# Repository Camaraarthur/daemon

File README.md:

<div align="center">
  
  <h1>daemon</h1>
  <p><strong>One AI agent. Terminal access to every device you own.</strong></p>
  <p>Open source &bull; Multi-device &bull; Free tier included &bull; Bring your own keys</p>

  <a href="https://daemon.page">Website</a> &bull;
  <a href="https://daemon.page/download">Download</a> &bull;
  <a href="SPEC.md">Spec</a> &bull;
  <a href="docs/">Docs</a>
</div>

---

## What is Daemon?

Daemon connects all your devices -- laptop, phone, server -- into one AI-powered workspace. Chat with your daemon, and it runs commands on any connected device, syncs your clipboard, deploys your apps, and remembers everything across sessions.

**Free tier**: Qwen3-Coder via OpenRouter. No credit card needed.
**Bring your own key**: Paste your Anthropic/OpenAI/DeepSeek key.
**Link Claude Max**: Use your $100/mo subscription through Daemon.

## Quick Start

```bash
# Install on any device (macOS, Linux, Windows)
curl -sSL daemon.page/install.sh | bash

# Pair with your account
daemon pair <CODE>  # Get code at daemon.page/download

# That's it. Your device is connected.
```

## Features

- **Multi-device mesh** -- Connect phone, laptop, server. Run commands on any device from anywhere.
- **Clipboard sync** -- Copy on your phone, paste on your laptop. Automatic.
- **One-click deploy** -- `/deploy` publishes to username.daemon.page instantly.
- **Persistent memory** -- Your daemon remembers across sessions. Never re-explain context.
- **Slash commands** -- `/commit`, `/deploy`, `/review`, `/search` -- power tools built in.
- **Your data stays yours** -- Local-first. Open source. Self-hostable.
- **Any model** -- Qwen (free), DeepSeek, Claude, GPT -- bring your own keys.
- **Native apps** -- Android, Windows, macOS, Linux. Same experience everywhere.

## How it works

<div align="center">
  
</div>

1. Install daemon on your devices
2. Each device connects via WebSocket to the daemon server
3. Chat with your AI -- it can run commands on any connected device
4. Deploy apps, sync files, search memory -- all through one conversation

## vs. Alternatives

| | Daemon | Claude Code | Cursor | Windsurf |
|---|---|---|---|---|
| Multi-device | All devices | One terminal | One IDE | One IDE |
| Free tier | Qwen unlimited | $20+/mo | $20/mo | $15/mo |
| Deploy apps | your.daemon.page | -- | -- | -- |
| Clipboard sync | Cross-device | -- | -- | -- |
| Memory | Persistent | Session only | -- | -- |
| Open source | MIT | -- | -- | -- |
| Self-hostable | Docker compose | -- | -- | -- |
| BYOK | Any provider | Anthropic only | Multiple | Multiple |

## Architecture

Daemon is a monorepo with four main components:

- **`web/`** -- Next.js web UI and API server (port 4800)
- **`cli/`** -- Cross-platform device bridge (Node.js)
- **`android/`** -- Native Android app (Kotlin/Jetpack Compose)
- **`desktop/`** -- Desktop bridge (Tauri/Rust)
- **`protocol/`** -- Shared protocol types (TypeScript)

The server coordinates WebSocket connections between devices and routes AI requests through a 3-tier model router (free Qwen -> mid DeepSeek -> premium Claude/GPT via BYOK).

See [SPEC.md](SPEC.md) for the full v0 specification (7,300 words covering protocol, security, agent architecture, and deployment).

## Self-hosting

```bash
git clone https://github.com/arthurcamara/daemon.git
cd daemon
docker compose up -d
```

Requires: Node.js 20+, SQLite. See [docs/](docs/) for detailed setup.

## Contributing

We welcome contributions. Daemon is built in the open.

- Read [CONTRIBUTING.md](CONTRIBUTING.md) before making changes
- Read [SPEC.md](SPEC.md) for architecture decisions
- Follow the rules in [CLAUDE.md](CLAUDE.md)

## License

[MIT](LICENSE) -- Copyright 2026 Arthur Camara

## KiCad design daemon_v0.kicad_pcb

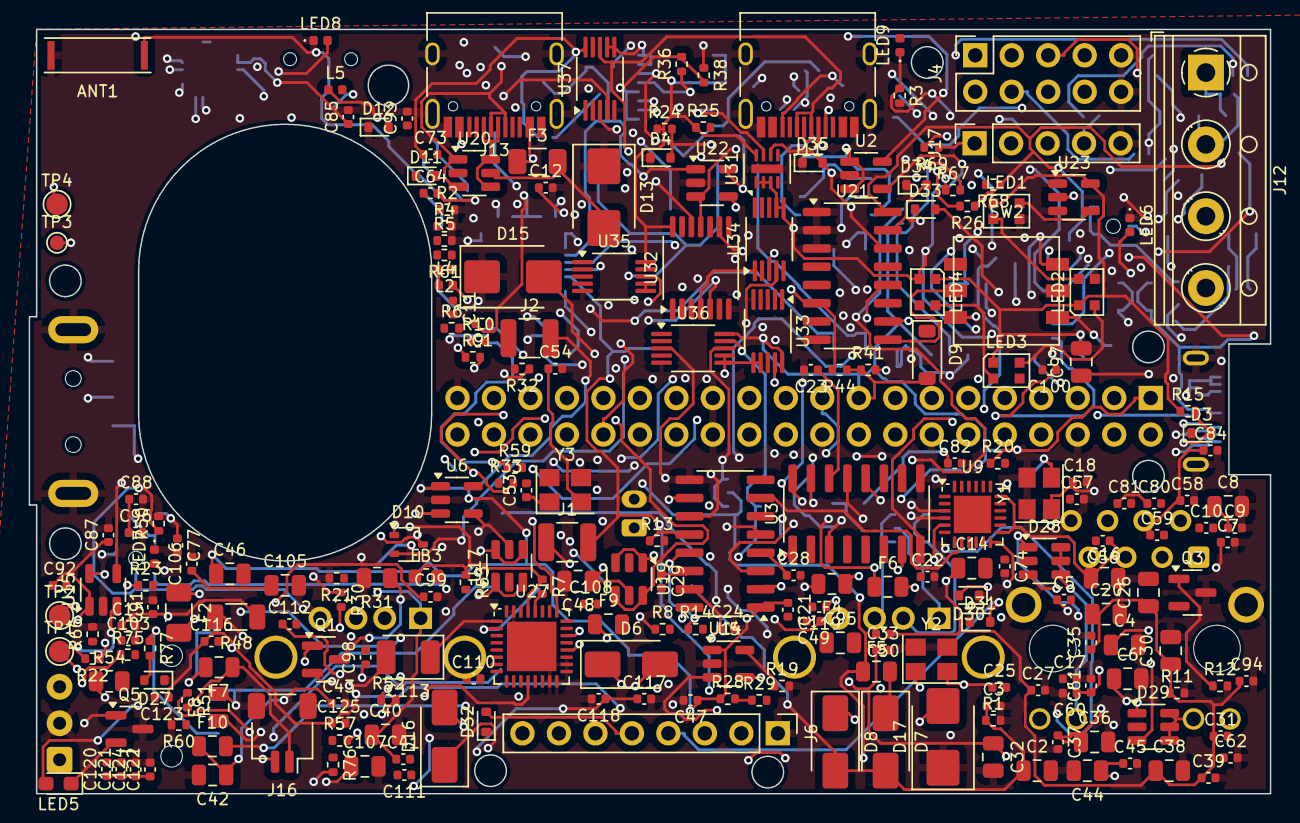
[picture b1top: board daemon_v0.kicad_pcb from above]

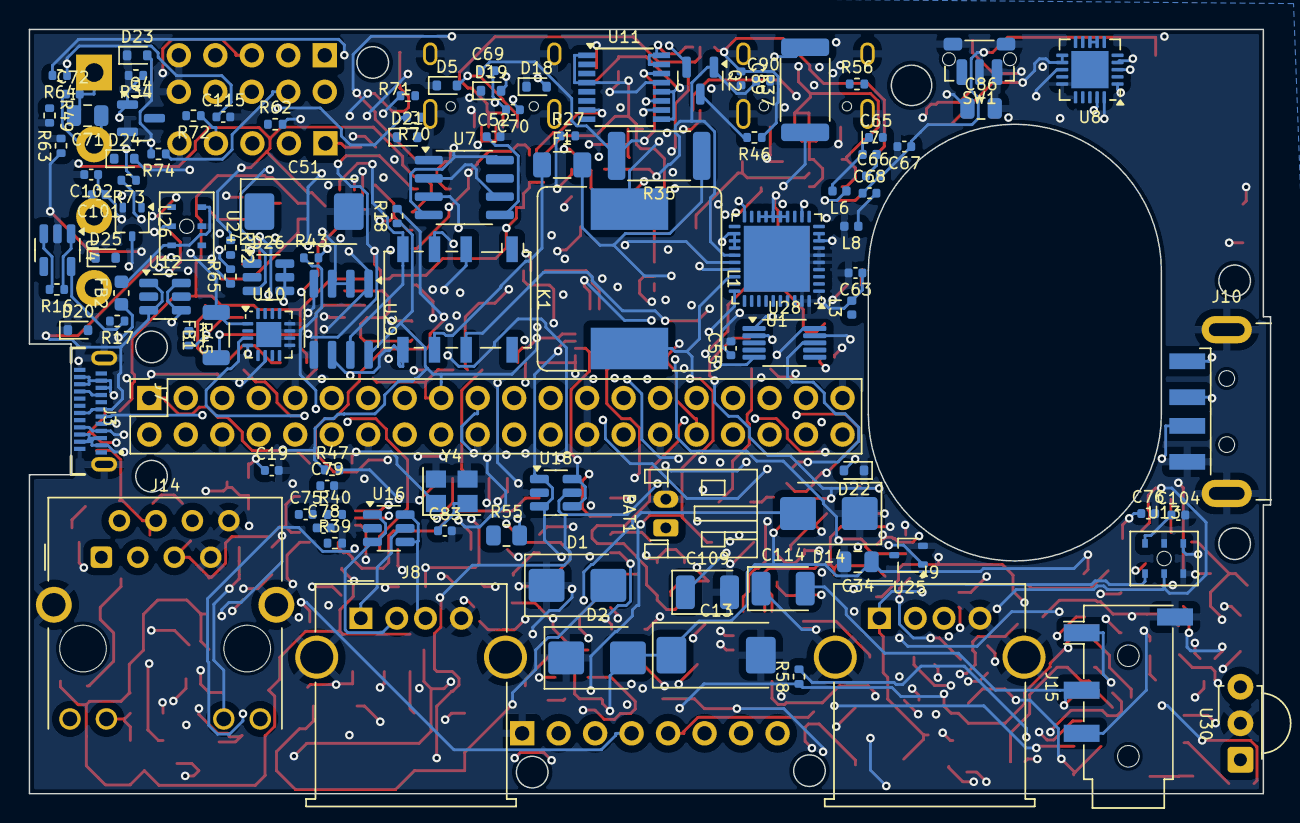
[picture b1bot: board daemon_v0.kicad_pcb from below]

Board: 4 copper layers, 86.4 x 53.2 mm, 338 parts (106 on the bottom side), 217 nets.

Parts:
ANT1: 915MHz Chip Antenna; Antenna_Chip_Johanson_0915AT43A0026
BAT1: Li-ion Battery; JST_PH_S2B-PH-K_1x02_P2.00mm_Horizontal
C1, C3, C5, C7, C9, C10, C11, C15, C17, C21, C22, C23, C27, C28, C29, C31, C33, C35, C37, C39, C41, C43, C45, C47, C49, C50, C55, C56, C57, C72, C73, C75, C77, C79, C81, C84, C85, C87, C88, C89, C90, C91, C92, C93, C94, C96, C100, C101, C102, C103, C104, C106, C108, C110, C115, C116, C117, C119, C120, C121, C122, C123, C124, C125: 100n; C_0402_1005Metric
C2, C4, C8, C14, C16, C20, C26, C30, C32, C34, C36, C38, C40, C42, C44, C46, C48, C71, C86, C95, C97, C105, C107: 10u; C_0805_2012Metric
C6: 22u; C_0805_2012Metric
C12, C74, C76, C78, C80, C118: 4u7; C_0402_1005Metric
C13, C51: 100u; CP_EIA-7343-31_Kemet-D
C18, C19, C24, C25: 22p; C_0402_1005Metric
C52, C69, C70: 10n; C_0402_1005Metric
C53, C54, C82, C83: 27p; C_0402_1005Metric
C58, C59, C60, C61, C66: 100p; C_0402_1005Metric
C62: 1p0; C_0402_1005Metric
C63, C64: 1p5; C_0402_1005Metric
C65: 3p3; C_0402_1005Metric
C67: 12p; C_0402_1005Metric
C68: 47p; C_0402_1005Metric
C98, C99: 1n; C_0402_1005Metric
C109, C113, C114: 100u; CP_EIA-3528-21_Kemet-B
C111, C112: 1u; C_0402_1005Metric
D1: TVS 5V_SYS Clamp; D_SMB
D2: TVS VIN Clamp; D_SMB
D3: ESD Port1 CC; D_SOD-523
D4: ESD Port5 CC1; D_SOD-523
D5: ESD Port5 CC2; D_SOD-523
D6: SS34 Charge Port1→VIN; D_SMA
D7: SS34 Charge Port4→VIN; D_SMA
D8: SS34 Charge Port5→VIN; D_SMA
D9: TVS ISO Input Clamp; D_SOD-123
D10: ESD Goobay CC1; SOT-323_SC-70
D11: ESD Goobay CC2; D_SOD-523
D12, D18, D19, D20, D21, D22, D23, D24, D25, D27, D30, D31, D32, D33, D34, D35: ESD5Z3.3; D_SOD-523
D13, D14, D15, D17: SMBJ5.0A; D_SMB
D16: SS34; D_SMA
D26, D28, D29: SM712; SOT-23-6
F1: PTC ISO Ch1 60Ω; Fuse_1206_3216Metric
F2: PTC ISO Ch2 60Ω; Fuse_1206_3216Metric
F3: PTC_1A; Fuse_1206_3216Metric
F4, F5, F6, F9, F10: PTC_500mA; Fuse_0805_2012Metric
F7, F8: PTC_200mA; Fuse_0805_2012Metric
FB1: 5V_AUDIO Ferrite 1.5A; L_1206_3216Metric
FB2: MIC_VDD Ferrite; L_0603_1608Metric
FB3: BLM18AG601SN1; L_0603_1608Metric
J1: Battery PTC 2A Fuse; R_1210_3225Metric
J2: 10mΩ Current Sense; R_1210_3225Metric
J3: 40-Pin Radxa Header; PinSocket_2x20_P2.54mm_Vertical
J4: AUX GPIO Breakout; PinSocket_2x05_P2.54mm_Vertical
J6: ST7789 SPI Display; MillMax_1x08_P2.54mm_Vertical
J7: USB-C♂ Plug → Radxa (KEY); USB_C_Plug_GCT_USB4155
J8: USB-A♀ Host Port 2; USB_A_Molex_67643_Horizontal
J9: USB-A♀ Host Port 3; USB_A_Molex_67643_Horizontal
J10: USB-A♂ Charge Port 4; USB_A_CNCTech_1001-011-01101_Horizontal
J11: USB-C♀ Main Port 5; USB_C_Receptacle_HRO_TYPE-C-31-M-12
J12: WAGO 4P Field Terminal; TerminalBlock_RND_205-00014_1x04_P5.00mm_Horizontal
J13: USB-C♀ Goobay Bridge; USB_C_Receptacle_HRO_TYPE-C-31-M-12
J14: RJ45 MagJack; RJ45_Hanrun_HR911105A_Horizontal
J15: TRRS 3.5mm Jack; Jack_3.5mm_PJ320D_Horizontal
J16: Speaker JST; JST_SH_SM02B-SRSS-TB_1x02-1MP_P1.00mm_Horizontal
J17: Analog-In; PinSocket_1x05_P2.54mm_Vertical
K1: G6K-2F-Y; Relay_DPDT_Omron_G6K-2F-Y
L1: 2.2uH Boost Inductor; L_Bourns_SRR1260
L2, L3, L6, L7: 12n; L_0402_1005Metric
L4, L5: 18n; L_0402_1005Metric
L8: 3n3; L_0402_1005Metric
LED1: WS2812B Status 1; LED_WS2812B-2020_PLCC4_2.0x2.0mm
LED2: WS2812B Status 2; LED_WS2812B-2020_PLCC4_2.0x2.0mm
LED3: WS2812B Status 3; LED_WS2812B-2020_PLCC4_2.0x2.0mm
LED4: WS2812B Status 4; LED_WS2812B-2020_PLCC4_2.0x2.0mm
LED5: IR Blaster LED; LED_0603_1608Metric_Pad1.05x0.95mm_HandSolder
LED6: Mic Recording Red 1; LED_0402_1005Metric
LED7: Mic Recording Red 2; LED_0402_1005Metric
LED8: Power Green LED; LED_0402_1005Metric
LED9: AMBER_0402; LED_0402_1005Metric
Q1: BC857 Dummy Load PNP; SOT-23
Q2: BSS84 Wake PMOS; SOT-23
Q3: 2N7002 PMIC Kill NMOS; SOT-23
Q4: AO3400A IR Drive NMOS; SOT-23
Q5: AO3400A; SOT-23
R1, R3, R4, R5, R49, R63: 100k; R_0402_1005Metric
R2, R11, R12, R16, R18, R20, R22, R26, R30, R33, R39, R40, R41, R42, R43, R44, R45, R46, R53, R57, R61, R62, R67, R68, R69, R70: 10k; R_0402_1005Metric
R6: 51k; R_0402_1005Metric
R7, R8: 4.7k; R_0402_1005Metric
R9, R10: 470; R_0402_1005Metric
R13, R14: 15k; R_0402_1005Metric
R15: 12k; R_0402_1005Metric
R17: 3.3k; R_0402_1005Metric
R19, R21, R23, R27: 13k; R_0402_1005Metric
R24, R25, R32: 56k; R_0402_1005Metric
R28, R50: 47k; R_0402_1005Metric
R29: 150; R_0402_1005Metric
R31: 82; R_0805_2012Metric
R34, R36: 562; R_0402_1005Metric
R35, R37: 562; R_2512_6332Metric
R38: 12.1k; R_0402_1005Metric
R47, R65, R66: 100; R_0402_1005Metric
R48: 100k; R_1206_3216Metric
R51, R52: 10R; R_0402_1005Metric
R54, R55: 1k; R_0805_2012Metric
R56, R71, R72, R73, R74, R75, R76, R77: 1k; R_0402_1005Metric
R58: 0R_DNP; R_0402_1005Metric
R59: 2.2k; R_0402_1005Metric
R60: 0; R_0402_1005Metric
R64: 120; R_0402_1005Metric
SW1: Power Button; SW_Push_1P1T-MP_NO_Horizontal_Alps_SKRTLAE010
SW2: 5-Way Nav Switch; SW_Alps_SKRHABE010
TP1: TP VIN; TestPoint_Pad_D1.5mm
TP2: TP BAT; TestPoint_Pad_D1.5mm
TP3: TP LX; TestPoint_Pad_D1.0mm
TP4: TP VSYS; TestPoint_Pad_D1.5mm
U1: IP5328P PMIC; QFN-40-1EP_6x6mm_P0.5mm_EP4.6x4.6mm
U2: AP2112K 3.3V LDO; SOT-23-5
U3: SL2.1A USB Hub 1; SOIC-16_3.9x9.9mm_P1.27mm
U4: SY6280 Port1 Radxa Key; SOT-23-5
U5: SY6280 Port2 USB-A♀; SOT-23-5
U6: SY6280 Port3 USB-A♀; SOT-23-5
U7: NE555 Heartbeat Timer; SOIC-8_3.9x4.9mm_P1.27mm
U8: CC1101 Sub-GHz Radio; QFN-20-1EP_4x4mm_P0.5mm_EP2.6x2.6mm
U9: RTL8152B Ethernet; QFN-24-1EP_4x4mm_P0.5mm_EP2.6x2.6mm
U10: MAX98357A I2S Amp; QFN-16-1EP_3x3mm_P0.5mm_EP1.75x1.75mm
U11: ISO1212 Dual Isolator; SSOP-16_3.9x4.9mm_P0.635mm
U12: ESD USB Port1; SOT-23-6
U13: INMP441 Mic Left; InvenSense_INMP441_BottomPort
U14: SL2.1A USB Hub 2; SOIC-16_3.9x9.9mm_P1.27mm
U15: SY6280 Port4 USB-A♂; SOT-23-5
U16: ESD USB Port2; SOT-23-6
U17: ESD USB Port3; SOT-23-6
U18: ESD USB Port4; SOT-23-6
U19: ESD USB Port5; SOT-23-6
U20: ESD Goobay Bridge; SOT-23-6
U21: PCF8574 I2C GPIO Exp; SOIC-16_3.9x9.9mm_P1.27mm
U22: SY6280 Port5 USB-C♀; SOT-23-5
U23: 3.3→5V Level Shifter; SOT-23-5
U24: INMP441 Mic Right; InvenSense_INMP441_BottomPort
U25, U26: ESD9B5.0ST5G; SOT-323_SC-70
U27: NAU88C22; QFN-32-1EP_5x5mm_P0.5mm_EP3.45x3.45mm
U28: ADS1115; MSOP-10_3x3mm_P0.5mm
U29: SP3485; SOIC-8_3.9x4.9mm_P1.27mm
U30: TSOP38238; Vishay_MINICAST-3Pin
U31: ATECC608B; DFN-8-1EP_2x3mm_P0.5mm_EP0.61x2.2mm
U32: 74LVC04A; TSSOP-14_4.4x5mm_P0.65mm
U33, U34, U35, U36, U37: TS3USB221; VSSOP-10_3x3mm_P0.5mm
Y1: 12MHz Hub1 Xtal; Crystal_SMD_3225-4Pin_3.2x2.5mm
Y2: 12MHz Hub2 Xtal; Crystal_SMD_3225-4Pin_3.2x2.5mm
Y3: 27MHz CC1101 Xtal; Crystal_SMD_3225-4Pin_3.2x2.5mm
Y4: 25MHz Ethernet Xtal; Crystal_SMD_3225-4Pin_3.2x2.5mm

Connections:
3V3_CLEAN: C16.1, C17.1, C56.1, C57.1, C58.1, C59.1, C60.1, C61.1, C84.1, C85.1, C86.1, J14.4, J14.5, R33.1, R40.1, U2.5, U8.7, U8.8, U8.11, U8.12, U8.19, U9.1, U9.10, U9.13, U9.18
3V3_J4_OUT: F9.2, J4.1
3V3_SYS: C73.1, C88.1, C89.1, C95.1, C96.1, C115.1, C116.1, C119.1, C120.1, C121.1, C122.1, C123.1, C124.1, C125.1, D9.2, F9.1, FB2.1, FB3.1, J3.1, J3.17, J6.2, K1.1, R7.1, R8.1, R18.1, R20.1, R22.1, R24.1, R25.1, R26.1, R41.1, R42.1, R43.1, R44.1, R45.1, R46.1, R47.1, R53.1, R58.1, R59.1, R64.1, R68.1, U11.1, U11.4, U21.16, U27.29, U28.8, U29.8, U31.8, U32.14, U33.10, U34.10, U35.10, U36.10, U37.10
5V_AUDIO: C97.1, C101.1, C102.1, FB1.2, U10.1
5V_J4_OUT: F10.2, J4.2
5V_SYS: C13.1, C14.1, C15.1, C20.1, C21.1, C26.1, C27.1, C30.1, C31.1, C34.1, C35.1, C38.1, C39.1, C42.1, C43.1, C46.1, C47.1, C50.1, C87.1, C90.1, C91.1, C92.1, C93.1, C94.1, D2.2, F10.1, FB1.1, J2.2, LED1.1, LED2.1, LED3.1, LED4.1, Q1.1, Q2.1, R11.1, R15.1, R16.1, R28.1, R48.1, U1.25, U2.1, U2.3, U3.1, U4.1, U5.1, U6.1, U7.4, U7.8, U9.11, U14.1, U15.1, U22.1, U23.5
ADC_ADDR: R63.1, U28.1
ADC_AIN0: D18.2, R69.2, U28.4
ADC_AIN0_P: J17.1, R69.1
ADC_AIN1: D19.2, R70.2, U28.5
ADC_AIN1_P: J17.2, R70.1
ADC_AIN2: D20.2, R71.2, U28.6
ADC_AIN2_P: J17.3, R71.1
ADC_AIN3: D21.2, R72.2, U28.7
ADC_AIN3_P: J17.4, R72.1
ADC_ALRT: R64.2, U28.2
AMP_OUT_N: R55.1, U10.13, U26.1
AMP_OUT_N_FILT: C99.1, R52.1, R55.2
AMP_OUT_P: R54.1, U10.15, U25.1
AMP_OUT_P_FILT: C98.1, R51.1, R54.2
AMP_SD: C100.1, R53.2, R56.2, U10.3
AUX_GPIO_1: D22.2, J3.8, R73.2, U29.4
AUX_GPIO_1_P: J4.3, R73.1
AUX_GPIO_2: D23.2, J3.10, R74.2, U29.1
AUX_GPIO_2_P: J4.4, R74.1
AUX_GPIO_3: D24.2, J3.11, R65.1, R75.2
AUX_GPIO_3_P: J4.5, R75.1
BAT: BAT1.1, C4.1, C5.1, D16.1, TP2.1
BAT_ISO: D17.2, J1.2, L1.2, U1.28
BAT_PROTECTED: D16.2, J1.1
BJT_BASE: Q1.2, R30.2
BJT_COLLECTOR: Q1.3, R31.1
CODEC_ADCOUT: R61.1, U27.24
CODEC_AVDD: C105.1, C106.1, FB3.2, U27.5
CODEC_DVDD: C107.1, C108.1, U27.20
CODEC_LHPOUT: C113.1, U27.1
CODEC_LMICN: R60.1, U27.6
CODEC_LMICP: C112.2, U27.7
CODEC_MICBIAS: C111.1, R62.1, U27.13
CODEC_RHPOUT: C114.1, U27.2
CODEC_VREF: C109.1, C110.1, U27.12
ETH_MDI_RXN: D29.3, J14.6, U9.5
ETH_MDI_RXP: D29.1, J14.3, U9.4
ETH_MDI_TXN: D28.3, J14.2, U9.3
ETH_MDI_TXP: D28.1, J14.1, U9.2
ETH_XI: C82.1, U9.21, Y4.1
ETH_XO: C83.1, U9.22, Y4.2
GND: ANT1.2, BAT1.2, C2.2, C3.2, C4.2, C5.2, C6.2, C7.2, C8.2, C9.2, C10.2, C11.2, C12.2, C13.2, C14.2, C15.2, C16.2, C17.2, C18.2, C19.2, C20.2, C21.2, C22.2, C23.2, C24.2, C25.2, C26.2, C27.2, C28.2, C29.2, C30.2, C31.2, C32.2, C33.2, C34.2, C35.2, C36.2, C37.2, C38.2, C39.2, C40.2, C41.2, C42.2, C43.2, C44.2, C45.2, C46.2, C47.2, C48.2, C49.2, C50.2, C51.2, C52.2, C53.2, C54.2, C55.2, C56.2, C57.2, C58.2, C59.2, C60.2, C61.2, C62.2, C63.2, C65.2, C67.2, C73.2, C74.2, C75.2, C76.2, C77.2, C78.2, C79.2, C80.2, C81.2, C82.2, C83.2, C84.2, C85.2, C86.2, C87.2, C88.2, C89.2, C90.2, C91.2, C92.2, C93.2, C94.2, C95.2, C96.2, C97.2, C98.2, C99.2, C100.2, C101.2, C102.2, C103.2, C104.2, C105.2, C106.2, C107.2, C108.2, C109.2, C110.2, C111.2, C115.2, C116.2, C117.2, C118.2, C119.2, C120.2, C121.2, C122.2, C123.2, C124.2, C125.2, D1.1, D2.1, D3.1, D4.1, D5.1, D11.1, D12.1, D13.1, D14.1, D15.1, D17.1, D18.1, D19.1, D20.1, D21.1, D22.1, D23.1, D24.1, D25.1, D26.2, D27.1, D28.2, D29.2, D30.1, D31.1, D32.1, D33.1, D34.1, D35.1, J3.6, J3.9, J3.14, J3.20, J3.25, J3.26, J3.30, J3.39, J4.9, J4.10, J6.1, J7.A1, J7.A8, J7.A12, J7.B1, J7.B5, J7.B8, J7.B12, J7.S1, J7.S2, J8.4, J8.5, J9.4, J9.5, J10.4, J10.5, J11.A1, J11.A8, J11.A12, J11.B1, J11.B8, J11.B12, J11.S1, J13.A1, J13.A8, J13.A12, J13.B1, J13.B8, J13.B12, J13.S1, J14.7, J14.8, J14.SH, J15.S, J16.MP, J17.5, L8.2, LED1.3, LED2.3, LED3.3, LED4.3, LED6.1, LED7.1, LED8.1, Q3.3, Q4.2, Q5.3, R1.2, R2.2, R3.2, R4.2, R5.2, R6.2, R11.2, R12.2, R13.2, R14.2, R17.2, R19.2, R21.2, R23.2, R27.2, R31.2, R32.2, R34.2, R39.2, R49.2, R50.2, R60.2, R63.2, R66.2, SW1.1, SW1.2, SW1.MP, SW2.Common, U1.1, U1.4, U1.5, U1.6, U1.7, U1.29, U1.38, U1.39, U1.40, U1.41, U2.2, U3.9, U4.2, U5.2, U6.2, U7.1, U8.14, U8.15, U8.16, U8.21, U9.6, U9.14, U9.15, U9.17, U9.20, U9.25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
GOOBAY_CC1: D11.2, J13.A5, U1.2
GOOBAY_CC2: D12.2, J13.B5, U1.3
GOOBAY_VBUS_FUSED: F3.1, J13.A4, J13.A9, J13.B4, J13.B9
HB_TMR_CTRL: C52.1, U7.5
HB_TMR_NODE_A: R28.2, R29.1, U7.7
HB_TMR_OUT: R30.1, U7.3
HB_TMR_THR: C51.1, R29.2, U7.2, U7.6
HUB1_DN_DM_1: U3.6, U33.4
HUB1_DN_DM_1_SW: J7.A7, J7.B7, U12.1, U12.3, U33.9
HUB1_DN_DM_2: U3.8, U34.4
HUB1_DN_DM_2_SW: J8.2, U16.1, U16.3, U34.9
HUB1_DN_DM_3: U3.11, U35.4
HUB1_DN_DM_3_SW: J9.2, U17.1, U17.3, U35.9
HUB1_DN_DM_4: U3.13, U14.3
HUB1_DN_DP_1: U3.5, U33.3
HUB1_DN_DP_1_SW: J7.A6, J7.B6, U12.4, U12.6, U33.8
HUB1_DN_DP_2: U3.7, U34.3
HUB1_DN_DP_2_SW: J8.3, U16.4, U16.6, U34.8
HUB1_DN_DP_3: U3.10, U35.3
HUB1_DN_DP_3_SW: J9.3, U17.4, U17.6, U35.8
HUB1_DN_DP_4: U3.12, U14.2
HUB1_VDD18: C23.1, U3.14
HUB1_VDD33: C22.1, U3.4
HUB1_XI: C18.1, U3.15, Y1.1
HUB1_XO: C19.1, U3.16, Y1.2
HUB2_DN_DM_1: U14.6, U36.4
HUB2_DN_DM_1_SW: J10.2, U18.1, U18.3, U36.9
HUB2_DN_DM_2: U9.7, U14.8
HUB2_DN_DM_3: U14.11, U37.4
HUB2_DN_DM_3_SW: J11.A7, J11.B7, U19.1, U19.3, U37.9
HUB2_DN_DM_4: R14.1, U14.13
HUB2_DN_DP_1: U14.5, U36.3
HUB2_DN_DP_1_SW: J10.3, U18.4, U18.6, U36.8
HUB2_DN_DP_2: U9.8, U14.7
HUB2_DN_DP_3: U14.10, U37.3
HUB2_DN_DP_3_SW: J11.A6, J11.B6, U19.4, U19.6, U37.8
HUB2_DN_DP_4: R13.1, U14.12
HUB2_VDD18: C29.1, U14.14
HUB2_VDD33: C28.1, U14.4
HUB2_XI: C24.1, U14.15, Y2.1
HUB2_XO: C25.1, U14.16, Y2.2
I2C1_PMIC_SCL: R10.2, U1.11
I2C1_PMIC_SDA: R9.2, U1.12
I2C1_SCL: D35.2, J3.5, R8.2, R10.1, U21.14, U27.27, U28.10, U31.6
I2C1_SDA: D34.2, J3.3, R7.2, R9.1, U21.15, U27.28, U28.9, U31.5
I2S_BCLK: J3.13, U10.7, U13.3, U24.3, U27.22
I2S_DATA_IN: J3.38, R50.1, R61.2, U13.5, U24.5
I2S_DATA_OUT: J3.40, U10.6, U27.25
I2S_LRCLK: J3.35, U10.8, U13.4, U24.4, U27.23
IP5328P_BST: C1.1, U1.19
IP5328P_LIGHT: LED9.1, R3.1, U1.20
IP5328P_NTC: R6.1, U1.10
IP5328P_RSET: R2.1, U1.21
IP5328P_VBUS: C8.1, C9.1, D13.2, F3.2, U1.32, U20.5
IP5328P_VBUSG: C10.1, U1.33
IP5328P_VING: C11.1, U1.31
IP5328P_VOUT1G: R4.1, U1.36
IP5328P_VOUT2G: R5.1, U1.35
IP5328P_VREG: C12.1, U1.27
IP5328P_VSYS: C6.1, C7.1, J2.1, TP4.1, U1.8, U1.9, U1.22, U1.23, U1.24, U1.34, U1.37
IR_GPIO: D25.2, Q5.1, R49.1, R76.2
IR_GPIO_P: J4.6, R76.1
IR_LED_N: LED5.1, Q5.2
IR_LED_P: LED5.2, R48.2
IR_RX: U21.12, U30.1
IR_VS_FILT: C117.1, C118.1, R68.2, U30.3
ISO_DO1: J3.28, U11.2
ISO_GND1: C69.2, C70.2, C71.2, C72.2, D10.2, J12.1, R36.2, R38.2, U11.9, U11.12
ISO_IN1: C69.1, R35.2, U11.14
ISO_IN1_PTCA: D10.1, F1.2, R35.1
ISO_IN1_RAW: F1.1, K1.6
ISO_IN2: C70.1, R37.2, U11.11
ISO_IN2_PTCA: D10.3, F2.2, R37.1
ISO_IN2_RAW: F2.1, K1.3
ISO_SENSE1: R36.1, U11.13
ISO_SENSE2: R38.1, U11.10
ISO_VCC1: C71.1, C72.1, J12.2
LED_DIN: LED1.4, U23.4
LX: C1.2, L1.1, TP3.1, U1.14, U1.15, U1.16, U1.17, U1.18
MCU_LED_DIN: J3.36, U23.2
MIC_LED_A: LED6.2, LED7.2, R57.2
MIC_VDD: C103.1, C104.1, FB2.2, R57.1, U13.1, U24.1, U24.6
NAV_CENTER: Q2.3, R46.2, SW2.Center, U21.9
NAV_DOWN: R43.2, SW2.C, U21.5
NAV_LEFT: R44.2, SW2.B, U21.6
NAV_RIGHT: R45.2, SW2.D, U21.7
NAV_UP: R42.2, SW2.A, U21.4
NC: D26.4, D26.5, D26.6, D28.4, D28.5, D28.6, D29.4, D29.5, D29.6, J7.A2, J7.A3, J7.A10, J7.A11, J7.B2, J7.B3, J7.B10, J7.B11, J14.9, J14.10, J14.11, J14.12, LED4.2, U2.4, U10.4, U11.7, U11.15, U11.16, U25.3, U26.3, U31.1, U31.2, U31.3, U31.7, U32.12, U33.6, U33.7, U34.6, U34.7, U35.6, U35.7, U36.6, U36.7, U37.6, U37.7
PCF8574_INT: J3.27, R47.2, U21.13
PMIC_KEY: Q2.2, Q3.2, SW1.1, U1.26
PMIC_KILL: J3.37, Q3.1, R12.1
PMIC_LIGHT_LED: LED9.2, R59.2
PWR_LED_A: LED8.2, R58.2
RADXA_GPIO_5V: J3.2, J3.4
RF_ANT: ANT1.1, C66.2, C67.1, C68.1
RF_ANT_N: L3.1, U8.9
RF_ANT_P: L2.1, U8.10
RF_ANT_PRE: C66.1, L7.2
RF_BAL_N: C63.1, L3.2, L5.1
RF_BAL_P: C62.1, C64.1, L2.2, L4.1
RF_CLK: J3.16, U8.1
RF_CS_N: J3.18, R33.2, U8.4
RF_DCOUPL: C55.1, U8.13
RF_FILT_MID: C65.1, L6.2, L7.1
RF_GDO0: U8.6, U21.11
RF_MISO: J3.15, U8.3
RF_MOSI: J3.12, U8.2
RF_NOTCH: C68.2, L8.1
RF_RBIAS: R32.1, U8.20
RF_SE_50: C64.2, L4.2, L5.2, L6.1
RF_XI: C53.1, U8.17, Y3.1
RF_XO: C54.1, U8.18, Y3.2
RLY_COIL_N: D9.1, K1.8, Q4.3
RS485_A: D26.1, J4.7, K1.5, R67.1, U29.6
RS485_B: D26.3, J4.8, K1.4, R67.2, U29.7
RS485_DE: R65.2, R66.1, U29.2, U29.3
RTL_AVDD10: C80.1, C81.1, U9.23
RTL_DVDD10: C78.1, C79.1, U9.16
RTL_DVDD10_UPS: C76.1, C77.1, U9.12
RTL_LANWAKEB: R40.2, U9.19
RTL_RSET: R39.1, U9.24
RTL_U2VDD10: C74.1, C75.1, U9.9
SCREEN_BL: J3.7, J6.8
SCREEN_DC: D33.2, J3.32, J6.6
SCREEN_RST: D32.2, J3.22, J6.5
SPI3_CLK: D30.2, J3.23, J6.3
SPI3_CS: J3.24, J6.7, R41.2
SPI3_MOSI: D31.2, J3.19, J6.4
SPK_N: F8.1, J16.2, R52.2
SPK_N_FUSED: C114.2, F8.2, J15.R1
SPK_P: F7.1, J16.1, R51.2
SPK_P_FUSED: C113.2, F7.2, J15.T
STINGER1_CC: D3.2, J7.A5, R15.2
STINGER5_CC1: D4.2, J11.A5, R24.2
STINGER5_CC2: D5.2, J11.B5, R25.2
STINGER_EN_1: J3.29, R16.2, U4.3, U32.1
STINGER_EN_2: J3.31, R18.2, U5.3, U32.3
STINGER_EN_3: J3.33, R20.2, U6.3, U32.5
STINGER_EN_4: J3.21, R22.2, U15.3, U32.9
STINGER_EN_5: R26.2, U21.10, U22.3, U32.11
STINGER_ISET_1: R17.1, U4.5
STINGER_ISET_2: R19.1, U5.5
STINGER_ISET_3: R21.1, U6.5
STINGER_ISET_4: R23.1, U15.5
STINGER_ISET_5: R27.1, U22.5
STINGER_OE_1: U32.2, U33.1
STINGER_OE_2: U32.4, U34.1
STINGER_OE_3: U32.6, U35.1
STINGER_OE_4: U32.8, U36.1
STINGER_OE_5: U32.10, U37.1
TRRS_RING2: C112.1, J15.R2, R62.2, R77.1
TRRS_RING2_P: D27.2, R77.2
USB_UP_DM: J13.A7, J13.B7, U3.3, U20.1, U20.3
USB_UP_DP: J13.A6, J13.B6, U3.2, U20.4, U20.6
USB_VBUS_1: C32.1, C33.1, F4.1, J7.A4, J7.A9, J7.B4, J7.B9, U4.4, U12.5
USB_VBUS_1_FUSED: D6.1, F4.2
USB_VBUS_2: C36.1, C37.1, D14.2, J8.1, U5.4, U16.5
USB_VBUS_3: C40.1, C41.1, D15.2, J9.1, U6.4, U17.5
USB_VBUS_4: C44.1, C45.1, F5.1, J10.1, U15.4, U18.5
USB_VBUS_4_FUSED: D7.1, F5.2
USB_VBUS_5: C48.1, C49.1, F6.1, J11.A4, J11.A9, J11.B4, J11.B9, U19.5, U22.4
USB_VBUS_5_FUSED: D8.1, F6.2
VIN: C2.1, C3.1, D1.2, D6.2, D7.2, D8.2, R1.1, TP1.1, U1.30
WAGO_COM1: J12.3, K1.7
WAGO_COM2: J12.4, K1.2
WAGO_MODE: J3.34, Q4.1, R34.1
WS2812B_DOUT_1: LED1.2, LED2.4
WS2812B_DOUT_2: LED2.2, LED3.4
WS2812B_DOUT_3: LED3.2, LED4.4

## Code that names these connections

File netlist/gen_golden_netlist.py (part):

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    "SPI3_CLK", "SPI3_MOSI",
    # RF SoftSPI bus (CC1101)
    "RF_CLK", "RF_MOSI", "RF_MISO",
    "RF_CS_N", "RF_GDO0", "RF_GDO2",  # GDO1 = SO pin (shared with RF_MISO)
    "RF_XI", "RF_XO", "RF_RBIAS", "RF_DCOUPL",
    "RF_ANT_P", "RF_ANT_N", "RF_ANT",
    # CC1101 filterbalun internal nodes (TI DN017 / SWRA168A 3-stage diff→SE→T-filter)
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    "AMP_OUT_P_FILT", "AMP_OUT_N_FILT",
    "AMP_SD", "SPK_P", "SPK_N", "MIC_VDD", "MIC_LED_A",
    # WS2812B + IR blaster
    "MCU_LED_DIN",  # 3.3V Radxa GPIO → 74AHCT1G125 level shifter input
    "LED_DIN",      # 5V output of level shifter → first WS2812B DIN
    "WS2812B_DOUT_1", "WS2812B_DOUT_2", "WS2812B_DOUT_3",
    "IR_GPIO", "IR_LED_P", "IR_LED_N",
    # Power indicator LED
    "PWR_LED_A",
    # AUX GPIO expansion
    "AUX_GPIO_1", "AUX_GPIO_2", "AUX_GPIO_3",  # AUX_GPIO_4 removed (sacrificed for STINGER_EN_3)
    # PCF8574 interrupt line (open-drain, pulled to 3V3_SYS; connect to GPIO for IRQ-driven nav)
    "PCF8574_INT",
    # Power UX (A6)
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    "ISO_IN1_RAW", "ISO_IN2_RAW",
    "ISO_IN1_PTCA", "ISO_IN2_PTCA",
    "ISO_IN1", "ISO_IN2",
    "ISO_SENSE1", "ISO_SENSE2",  # SENSE pins: R_SENSE connects SENSE→FGND for threshold setting
    "ISO_SUB1", "ISO_SUB2",      # SUB pins: floating copper islands (isolation barrier)
    "ISO_DO1", "ISO_DO2",
    # Heartbeat timer (G)
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    "STINGER1_CC",
    # Radxa GPIO 5V rail (pins 2,4) — intentionally NOT connected to 5V_SYS.
    # Radxa outputs its own 5V here once running; we isolate it from Daemon's rail.
    "RADXA_GPIO_5V",
    # NAU88C22 audio codec (L)
    "CODEC_LHPOUT", "CODEC_RHPOUT", "CODEC_LSPKOUT", "CODEC_RSPKOUT",
    "CODEC_LMICP", "CODEC_LMICN", "CODEC_RMICP", "CODEC_RMICN",
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    # ADC protected inputs
    "ADC_AIN0_P", "ADC_AIN1_P", "ADC_AIN2_P", "ADC_AIN3_P",
    # GPIO protected
    "AUX_GPIO_1_P", "AUX_GPIO_2_P", "AUX_GPIO_3_P", "IR_GPIO_P",
    # Audio protected
    "SPK_P_FUSED", "SPK_N_FUSED", "TRRS_RING2_P",
    # Ethernet protected
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    # J4 fused power outputs
    "3V3_J4_OUT", "5V_J4_OUT",
    # WAGO switchable bypass
    "WAGO_COM1", "WAGO_COM2",  # Relay common pins (from WAGO pins 3/4)
    "WAGO_MODE",               # GPIO: LOW=industrial, HIGH=RS-485
    "RLY_COIL_N",              # Relay coil negative (BSS138 drain)
]

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    #   Pins 24,25: VSP/VSN (current sense)
    #   Pin 26:     KEY (button)
    #   Pin 27:     VREG (internal 3.1V LDO)
    #   Pin 28:     BAT (battery)
    #   Pin 29:     AGND (analog ground)
    #   Pin 30:     VIN (micro-USB input detect)
    #   Pin 31:     VING (VIN PMOS gate)
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    # Physical power button
    add(_next_ref("SW"), "SW_PWR", FP_SW_PUSH, "Switch", "SW_Push",
        [("1","PMIC_KEY"),("2","GND"),("MP","GND")])
    # J5 (PWR_MGMT header) removed — PMIC_KILL now routed via J3 pin 37
    # Software reboot: `sudo reboot` (warm SoC reset, no PMIC needed)
    # Software shutdown: drive J3.37 HIGH → Q3 pulls PMIC_KEY → IP5328P off

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        # DFP host: Rp pull-up (12k → 1.5A per USB-C Table 4-25) + higher ISET (3.3k → 2.06A)
        # D+/D- → Hub1 port 1 downstream: Radxa appears as USB device to laptop via Goobay.
        # Removing this plug from the Radxa cuts all power to the SBC — physical key.
        # Stinger GPIOs (STINGER_EN_1-5 via J3) control power switches — no USB host needed.
        ("U4",  1, FP_USB_C_PLUG,   "Connector", "USB_C_Plug_USB2.0",
         "HUB1_DN_DP_1", "HUB1_DN_DM_1", True,  "Rp", "3.3k"),
        ("U5",  2, FP_USB_A_FEMALE, "Connector", "USB_A",
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         ("A0","GND"),("A1","GND"),("A2","GND"),
         ("P0","NAV_UP"),("P1","NAV_DOWN"),("P2","NAV_LEFT"),("P3","NAV_RIGHT"),
         ("P4","NAV_CENTER"),
         ("P5","STINGER_EN_5"),  # GPIO-controlled USB-C female port 5 enable
         ("P6","RF_GDO0"),      # CC1101 interrupt (sync word / RX ready)
         ("P7","IR_RX"),         # IR receiver (TSOP38238) demodulated output
         ("INT","PCF8574_INT")])
    # PCF8574 bypass cap
    add(_next_ref("C"), "100n", FP_C0402, "Device", "C", [("1","3V3_SYS"),("2","GND")])
    # PCF8574 INT pull-up (10k to 3V3_SYS) — open-drain; keeps INT high (inactive) when no nav
    # event. Wire PCF8574_INT to a Radxa GPIO to enable interrupt-driven nav detection.
    add(_next_ref("R"), "10k", FP_R0402, "Device", "R", [("1","3V3_SYS"),("2","PCF8574_INT")])

    # ======================================================================
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    add(_next_ref("LED"), "VSMB294008", FP_IR_LED, "Device", "LED",
        [("A","IR_LED_P"),("K","IR_LED_N")])
    add(_next_ref("Q"), "AO3400A", FP_NFET_SOT23, "Device", "Q_NMOS_GDS",
        [("G","IR_GPIO"),("D","IR_LED_N"),("S","GND")])
    # IR LED current limit: need to stay within resistor rating for worst-case DC stuck-on.
    # 100Ω → I=38mA, P=0.14W → use 1206 (0.25W, ample margin). 38mA is still good for IR blast.
    add(_next_ref("R"), "100", "Resistor_SMD:R_1206_3216Metric", "Device", "R",
        [("1","5V_SYS"),("2","IR_LED_P")])
    # IR_GPIO pull-down (100k) — prevent spurious IR flash during Radxa boot
    add(_next_ref("R"), "100k", FP_R0402, "Device", "R",
        [("1","IR_GPIO"),("2","GND")])

    # ======================================================================
    # F: 40-Pin Radxa Expansion Header (PinSocket)
    # ======================================================================
    add("J3", "Radxa-40Pin", FP_RADXA_HDR, "Connector_Generic", "Conn_02x20_Odd_Even",
        [("1","3V3_SYS"),        ("2","RADXA_GPIO_5V"),
         ("3","I2C1_SDA"),       ("4","RADXA_GPIO_5V"),
         ("5","I2C1_SCL"),  ("6","GND"),
         ("7","SCREEN_BL"), ("8","AUX_GPIO_1"),   # was NAV_UP (→ PCF8574)
         ("9","GND"),       ("10","AUX_GPIO_2"),   # was NAV_DOWN (→ PCF8574)
         ("11","AUX_GPIO_3"),("12","RF_MOSI"),      # GPIO3_A2/I2S3_MCLK — soft SPI (not BCLK!)
         ("13","I2S_BCLK"),  ("14","GND"),         # GPIO3_A3/I2S3_SCLK_M0 — HW I2S bit clock
         ("15","RF_MISO"),  ("16","RF_CLK"),
         ("17","3V3_SYS"),  ("18","RF_CS_N"),
         ("19","SPI3_MOSI"),("20","GND"),
         ("21","STINGER_EN_4"),("22","SCREEN_RST"),
         ("23","SPI3_CLK"), ("24","SPI3_CS"),
         ("25","GND"),      ("26","GND"),              # Pin 26 = NC on Radxa Zero 3W
         ("27","PCF8574_INT"),("28","ISO_DO1"),  # Pin 27=PCF8574 IRQ, Pin 28=ISO1212 output 1
         ("29","STINGER_EN_1"),("30","GND"),
         ("31","STINGER_EN_2"),("32","SCREEN_DC"),
         ("33","STINGER_EN_3"),("34","WAGO_MODE"),     # GPIO: LOW=industrial, HIGH=RS-485 relay
         ("35","I2S_LRCLK"),("36","MCU_LED_DIN"),  # 3.3V → level shifter input
         ("37","PMIC_KILL"),("38","I2S_DATA_IN"),   # was NAV_CENTER (→ PCF8574+BSS84)
         ("39","GND"),      ("40","I2S_DATA_OUT")])
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    # The daemon agent decides what each pin does at runtime.
    add("J4", "DAEMON-IO", FP_CONN_2X05, "Connector_Generic", "Conn_02x05_Odd_Even",
        [("1","3V3_J4_OUT"),   ("2","5V_J4_OUT"),    # PTC-fused power out
         ("3","AUX_GPIO_1_P"), ("4","AUX_GPIO_2_P"), # Protected GPIO
         ("5","AUX_GPIO_3_P"), ("6","IR_GPIO_P"),    # Protected GPIO
         ("7","RS485_A"),      ("8","RS485_B"),       # SM712 TVS protected
         ("9","GND"),          ("10","GND")])

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    # Firmware shuts down amp (SD_MODE LOW) when headphones detected, enables for speaker.
    # With 100k pull-up and internal 100k pull-down: V = 3.3 × 100k/(100k+100k) = 1.65V
    # 1.65V = left channel at +12dB (per MAX98357A datasheet Table 1). Perfect for mono speaker.
    # To shut down: firmware drives AMP_SD LOW via a GPIO (connect to a Radxa GPIO).
    # For V0: just use pull-up, amp always on, firmware controls via I2C to codec.
    add(_next_ref("R"), "100k", FP_R0402, "Device", "R",
        [("1","3V3_SYS"),("2","AMP_SD")])
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         ("VREF","CODEC_VREF"),("MICBIAS","CODEC_MICBIAS"),
         ("AGND","GND"),("R2P","GND"),("R2N","GND"),("L2P","GND"),("L2N","GND"),
         ("DGND","GND"),("DVDD","CODEC_DVDD"),
         ("MCLK","RF_MOSI"),    # Shares GPIO3_A2 (J3 pin 12) with CC1101 SoftSPI MOSI.
         # Radxa pin-muxes: MCLK mode for audio, SPI mode for RF. Not simultaneous.
         ("BCLK","I2S_BCLK"),("FS","I2S_LRCLK"),
         ("ADCOUT","CODEC_ADCOUT"),  # Separate net — NOT on I2S_DATA_IN to avoid bus fight with INMP441s
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    # ======================================================================
    # N: SP3485 — RS-485 Transceiver (Modbus / DMX-512)
    # ======================================================================
    # Half-duplex RS-485. UART2 TX/RX on AUX_GPIO_1/2, DE on AUX_GPIO_3.
    # SP3485EN SOIC-8 pin map:
    #   1:RO 2:RE 3:DE 4:DI 5:GND 6:A 7:B 8:VCC
    add("U29", "SP3485", FP_SP3485, "Interface_UART", "SP3485",
        [("RO","AUX_GPIO_2"),  # Receiver output → UART2_RX (Radxa pin 10)
         ("RE","RS485_DE"),     # Receiver enable (active low) — tied to DE for half-duplex
         ("DE","RS485_DE"),     # Driver enable (active high)
         ("DI","AUX_GPIO_1"),   # Driver input → UART2_TX (Radxa pin 8)
         ("GND","GND"),("A","RS485_A"),("B","RS485_B"),("VCC","3V3_SYS")])
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
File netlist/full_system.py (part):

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    · IP5328P (QFN-40): high-current boost converter + Li-ion charger + I2C telemetry
    · 4.7µH high-current boost inductor (Isat > 5A) on the SW node
    · DFT test points TP1–TP4 and 0Ω isolation jumpers J1/J2
    · KEY pin wired to PMIC_KEY net (shared with A6 power UX circuit)
    · LED1/LED2/LED3 REMOVED (ECO #2026-03-E: I2C bus clamping conflict)

  Subsystem A5 – Goobay 74446 USB-C Mechanical Bridge
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
  Subsystem A6 – Advanced Power UX (ECO #2026-03-D)
    · BSS84 PMOS wake-blocker: NAV_CENTER wakes when 5V OFF; isolated when ON
    · 2N7002 NMOS software kill: Radxa PMIC_KILL GPIO simulates double-tap
    · SW_PWR tactile button: always-on hard wake/sleep; SW_PWR_GPIO for long-press
    · 3-pin Power Management Header: PMIC_KILL / SW_PWR_GPIO / GND

  Subsystem C  – Stinger Ports (4 × SY6280AAC power-distribution switch)
    · One SY6280AAC (SOT-23-5) per stinger USB port + USBLC6-2SC6 ESD
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    · Replaces breakout analog joystick + ADS1015 I2C ADC

  Subsystem E2 – WS2812B Smart RGB LEDs × 4 (NEW)
    · Daisy-chained; data-in on LED_DIN (Radxa header pin 36)
    · 100 nF bypass per LED; 5V_SYS supply

  Subsystem E3 – Stealth IR Blaster (NEW)
    · VSMB294008 side-view SMD IR LED; front-edge placement
    · AO3400A N-MOSFET driver (Gate = IR_GPIO, Drain = LED−, Source = GND; ECO #2026-03-F)

  Subsystem F  – 40-Pin Radxa Expansion Header
    · 2×20 P2.54 mm connector; Raspberry Pi HAT / Radxa pinout
    · All 40 pins named: power rails, SPI3 (display), SoftSPI (CC1101),
      I2C1 (pins 3/5), I2S/PCM, screen BL/DC/RST, Stinger EN/FLAG, LED_DIN

  Subsystem G  – NE555 Heartbeat / Dummy-Load (SM-PWR-02)

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def _build_power_system(
    gnd: Net,
    vcc_5v: Net,
    i2c1_sda: Net,   # Radxa pin 3 – IP5328P SDA telemetry (I2C1, Always-On)
    i2c1_scl: Net,   # Radxa pin 5 – IP5328P SCL telemetry (I2C1, Always-On)
    key_net: Net,    # PMIC_KEY: shared with A6 power UX (PMOS/NMOS/SW_PWR)
) -> dict[str, Net]:
    """
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
    # ── IC power ──────────────────────────────────────────────────────────────
    ic["VIN"]  += vin
    ic["BAT"]  += bat_iso         # BAT pin sits behind J1 isolation jumper
    ic["SW"]   += sw
    ic["VOUT"] += vout
    ic["GND"]  += gnd             # QFN-40 exposed pad + GND pins
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    r_i2c_scl      = Resistor(value="470")
    i2c1_pmic_sda  = Net("I2C1_PMIC_SDA")   # IP5328P SDA (protected side of series resistor)
    i2c1_pmic_scl  = Net("I2C1_PMIC_SCL")   # IP5328P SCL (protected side of series resistor)
    r_i2c_sda[1] += i2c1_sda          # Radxa header side (pin 3)
    r_i2c_sda[2] += i2c1_pmic_sda     # IP5328P side
    r_i2c_scl[1] += i2c1_scl          # Radxa header side (pin 5)
    r_i2c_scl[2] += i2c1_pmic_scl     # IP5328P side
    ic["SDA"]  += i2c1_pmic_sda        # IP5328P I2C telemetry (via 470Ω protection)
    ic["SCL"]  += i2c1_pmic_scl        # IP5328P I2C telemetry (via 470Ω protection)
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    bat_conn[2] += gnd      # cell negative

    # ── Isolation jumpers ────────────────────────────────────────────────────
    J1[1] += bat            # BAT (raw) → J1 → BAT_ISO → IC pin 6
    J1[2] += bat_iso
    J2[1] += vout           # VOUT (raw) → J2 → VOUT_ISO → 5V_SYS
    J2[2] += vout_iso
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    Instantiate the Alps SKRHABE010 5-way navigation switch.

    Pin mapping (SKRHABE010 datasheet Drawing No.2):
      Pin 1 (A)      → NAV_UP       (direction; exact mapping depends on mounting rotation)
      Pin 2 (Center)  → NAV_CENTER   (center push)
      Pin 3 (C)      → NAV_DOWN
      Pin 4 (B)      → NAV_LEFT
      Pin 5 (Common) → GND           (shared return for all 5 switches)
      Pin 6 (D)      → NAV_RIGHT

    All switches are active-low: pressed → pin shorted to Common (GND).
    10 kΩ pull-ups to 3V3_SYS keep each line high when idle.
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    as a direction press, not a center press.

    Radxa header GPIO assignments (ECO #2026-03-NAV):
      NAV_UP     → pin 8  (was STINGER_FLAG_2; flags now polled via USB hub)
      NAV_DOWN   → pin 10 (was STINGER_FLAG_3)
      NAV_LEFT   → pin 11 (was STINGER_FLAG_1)
      NAV_RIGHT  → pin 33 (was STINGER_EN_3; port 3 always-on via 10k pull-up)
      NAV_CENTER → pin 37 (was JOY_SW; same GPIO, same wake-blocker wiring)
    """
    Resistor = Part("Device", "R", dest=TEMPLATE, footprint=FP_R0402)

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    screen_rst: Net,
    screen_bl:  Net,
    # Navigation switch (ECO #2026-03-NAV: replaces analog joystick)
    nav_up:     Net,    # pin 8  (was STINGER_FLAG_2)
    nav_down:   Net,    # pin 10 (was STINGER_FLAG_3)
    nav_left:   Net,    # pin 11 (was STINGER_FLAG_1)
    nav_right:  Net,    # pin 33 (was STINGER_EN_3)
    nav_center: Net,    # pin 37 (was JOY_SW)
    # SoftSPI bus (bit-banged; CC1101 on free GPIOs to avoid SPI0 collision)
    soft_spi_sck:  Net,   # RF_CLK  → pin 16
    soft_spi_mosi: Net,   # RF_MOSI → pin 13
    soft_spi_miso: Net,   # RF_MISO → pin 15
    # Stinger port enable GPIOs (3 of 4; EN_3 sacrificed for NAV_RIGHT)
    stinger_en:   list[Net],   # len == 4 (only [0],[1],[3] on header; [2] always-on)
    # I2C1 bus (IP5328P telemetry – pins 3/5)
    i2c1_sda:   Net,
    i2c1_scl:   Net,
    # SPI chip selects for protocol analyzer subsystems (H, J)
    rf_cs_n:    Net,    # CC1101 SPI chip select      (pin 18)
    # ECO #2026-02-V2: CAN bus removed; pin 36 → WS2812B LED data chain
    led_din:    Net,    # WS2812B data chain DIN       (pin 36)
) -> None:
    """
    Instantiate the 2×20 Radxa expansion header and name every pin.
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    Physical layout (Raspberry Pi / Radxa compatible):
    ┌────┬─────────────────────────────────┬────┐
    │  1 │ 3V3_SYS              5V_SYS     │  2 │
    │  3 │ I2C1_SDA (GPIO2)     5V_SYS     │  4 │
    │  5 │ I2C1_SCL (GPIO3)     GND        │  6 │
    │  7 │ SCREEN_BL (GPIO4)    NAV_UP     │  8 │
    │  9 │ GND                  NAV_DOWN   │ 10 │
    │ 11 │ NAV_LEFT             I2S_BCLK   │ 12 │
    │ 13 │ RF_MOSI (SoftSPI)    GND        │ 14 │
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    │ 31 │ STINGER_EN_2         SCREEN_DC  │ 32 │
    │ 33 │ NAV_RIGHT            GND        │ 34 │
    │ 35 │ I2S_LRCLK            LED_DIN    │ 36 │
    │ 37 │ NAV_CENTER (GPIO26)  I2S_DATA_IN│ 38 │
    │ 39 │ GND                  I2S_DATA_OUT│ 40 │
    └────┴─────────────────────────────────┴────┘

    ECO #2026-03-NAV changes:
    · Pins 8/10/11 repurposed: STINGER_FLAG_1/2/3 → NAV_UP/DOWN/LEFT.
      Stinger overcurrent is now polled via SL2.1A USB hub status registers
      (the OC_N lines still connect to the hub IC; only the Radxa GPIO
      monitoring path is removed).
    · Pin 33 repurposed: STINGER_EN_3 → NAV_RIGHT.
      Port 3 (USB-A female) stays always-on via the 10 kΩ EN pull-up to
      3V3_SYS in _build_stinger_port. Firmware cannot individually disable
      port 3; this is acceptable for a device-input receptacle.
    · Pin 37: JOY_SW → NAV_CENTER (same GPIO, same BSS84 wake-blocker wiring).

    PIN LOCK — NO OVERLAP CONFIRMED:
        Screen  = SPI3  (pins 19/23/24 — SPI3_MOSI/CLK/CS; pin 21 → STINGER_EN_4)
        Audio   = I2S0  (pins 12/35/38/40 — PCM_CLK/LRCK/DIN/DOUT)
        RF      = SoftSPI (pins 13/15/16 + CS on 18)
        Nav     = pins 8/10/11/33/37 (5-way switch, all digital GPIO)
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    # If VCCIO = 3.3V: no action required.
    conn[3]  += i2c1_sda
    conn[5]  += i2c1_scl
    conn[7]  += screen_bl         # SCREEN_BL → GPIO4 (hardware PWM)
    conn[9]  += gnd
    conn[11] += nav_left          # NAV_LEFT (ECO #2026-03-NAV; was STINGER_FLAG_1)
    conn[13] += soft_spi_mosi     # RF_MOSI (ECO #2026-03-F: safe GPIO)
    conn[15] += soft_spi_miso     # RF_MISO (ECO #2026-03-F: safe GPIO)
    conn[17] += vcc_3v3
    conn[19] += spi_mosi          # SPI3_MOSI → screen SDA
    conn[21] += stinger_en[3]     # STINGER_EN_4 (was SPI3_MISO; screen doesn't use it)
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    conn[31] += stinger_en[1]     # STINGER_EN_2
    conn[33] += nav_right         # NAV_RIGHT (ECO #2026-03-NAV; was STINGER_EN_3)
    conn[35] += i2s_lrclk         # I2S3_LRCK_M0 exclusively
    conn[37] += nav_center        # NAV_CENTER (ECO #2026-03-NAV; was JOY_SW / GPIO26)
    conn[39] += gnd

    # ── Even column (pins 2, 4, 6 … 40) ──────────────────────────────────────
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    conn[16] += soft_spi_sck      # RF_CLK (ECO #2026-03-F)
    conn[18] += rf_cs_n           # RF_CS_N (ECO #2026-03-F)
    conn[20] += gnd
    conn[22] += screen_rst        # SCREEN_RST (GPIO25)
    conn[24] += screen_cs         # SPI3_CS0 → screen CS
    conn[26] += gnd               # NC/GND (Radxa SoC pin NC)
    conn[28] += gnd               # NC/GND (ECO #2026-03-H: pin disconnected on Zero 3W)
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    c_byp = Capacitor(value="10n")         # control-voltage bypass (pin 5)

    # ── Internal nets ─────────────────────────────────────────────────────────
    tmr_out  = Net("HB_TMR_OUT")    # 555 output (pin 3)
    tmr_ctrl = Net("HB_TMR_CTRL")  # 555 control voltage (pin 5 bypass to GND)
    tmr_thr  = Net("HB_TMR_THR")   # threshold / trigger / discharge junction

    # ── 555 power ─────────────────────────────────────────────────────────────
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    gnd: Net,
    vcc_5v: Net,
    nav_center: Net,     # NAV_CENTER net → PMOS drain (wake source; ECO #2026-03-NAV)
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
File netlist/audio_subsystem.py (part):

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    i2s_din = Net("I2S_DATA_IN")    # microphone → MCU

    # I2S bus: Radxa Zero 3W is the I2S master.  These nets are shared by name
    # with full_system.py (I2S_BCLK=pin 12, I2S_LRCLK=pin 35, I2S_DATA_IN=pin 38,
    # I2S_DATA_OUT=pin 40).  No MCU Part instantiation is needed here; the Radxa
    # header in full_system.py connects the SoC's I2S3 peripheral to these nets.

    # Amplifier I2S inputs
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    trrs_jack["Ring1Switch"] += btl_filt_n  # pin 11                   (was btl_out_n)

    # The output side of the NC switches drives the JST-SH speaker connector.
    # When the plug is absent the path is: AMP_OUT_P → NC switch → speaker pin 1
    #                                      AMP_OUT_N → NC switch → speaker pin 2
    speaker_conn[1] += trrs_jack["Tip"]    # pin 2 (wiper) – speaker positive
    speaker_conn[2] += trrs_jack["Ring1"]  # pin 3 (wiper) – speaker negative

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
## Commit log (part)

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2026-02-23 chore: initial commit before Step 2 fixes
2026-02-23 fix: RF Balun network and ADS1015 Analog Domain Offload
2026-02-23 feat: change Stinger port footprint to USB-A Male Plug
2026-02-23 feat: configure Stinger port 1 as Male Plug and ports 2/3 as Female
2026-02-28 feat: add hardware-aware agent daemon with complete HAL and spec database
    Implements the full software stack for the Daemon V0 custom PCB HAT
    (Radxa Zero 3W / RK3566), covering all 14+ hardware subsystems:
    HAL drivers (hal/):
    - Circuit breaker base class with exponential backoff fault tolerance
    - IP5328P PMIC (I2C 0x75): battery telemetry, SoC estimation, boost control
    - CC1101 sub-GHz RF (spi-gpio per ECO mandate): 915MHz 2-GFSK, SmartRF preset
2026-02-28 fix: critical watchdog bug + hardened daemon architecture
    Deep research-driven improvements to the hardware agent daemon:
    CRITICAL BUG FIX:
    - systemd service had WatchdogSec=30 but code never called sd_notify(),
    causing either restart loops or dead watchdog. Fixed with sdnotify
    integration: READY=1 after probe cascade, WATCHDOG=1 every tick,
    STOPPING=1 on shutdown. Changed Type=simple → Type=notify.
2026-02-28 fix: PowerStateMachine classify bug + circuit breaker recovery reset
    Round 2 research findings:
    1. PowerStateMachine._classify() had inverted iteration logic — voltages
    were being classified against thresholds incorrectly. Refactored to
    use explicit TRANSITIONS dict with separate drop/rise thresholds and
    walks adjacent states downward then upward. Verified with comprehensive
    discharge/charge/oscillation tests.
2026-03-21 fix: flip J6 screen connector to B.Cu — female socket on back side
2026-03-21 fix: J6 screen connector — PinHeader through-hole pads for Mill-Max receptacles
2026-03-21 fix: add WAGO 3D model from Downloads, fix model references
2026-03-21 fix: J6 screen connector — bare holes footprint (no 3D pin model)
2026-03-21 fix: correct rotation on all 23 back-side components (flip negated rotation)
2026-03-21 fix: restore board from screenshot4 (disk full corrupted file) + J6 rotated 180°
2026-03-22 fix: replace fake WAGO footprint with real Phoenix PT-1.5-3 screw terminal (3D model included)
2026-03-22 feat: 4-position Phoenix PT screw terminal (GND + 3V3 + 2 signal channels)
2026-03-22 feat: Freerouting partial autoroute — ~100 nets routed, 406 need manual routing
2026-03-22 feat: Phoenix PTSM push-in spring terminal — 5mm tall, no tools, official STEP model
2026-03-22 chore: clear all routing + switch to KF301 5mm screw terminal (JLCPCB available)
2026-03-22 fix: restore placements from screenshot4 (import had reset to grid)
2026-03-22 fix: antenna footprint was 3.2x1.6mm, actual is 7.0x2.0mm (from datasheet)
2026-03-22 feat: screenshot5 placements + fixed antenna footprint (7x2mm) + keep-out zone
2026-03-22 fix: INMP441 footprint WRONG — pitch was 1.47mm (should be 1.33mm), pads were 0.62x0.77 (should be 0.40x0.60)
2026-03-22 feat: re-import with fixed footprints (antenna 7mm, INMP441 1.33mm pitch, PJ-320D 3.5mm jack)
2026-03-22 fix: TRRS mic protection was dead-end stub — now 1k+TVS protects codec input
2026-03-22 chore: board ready for routing — screenshot7 placements, zones, 4 layers, DSN exported
2026-03-22 feat: Freerouting v1.9 complete — 1817 traces, 173 vias, 3 min routing
2026-03-22 fix: add antenna copper keepout zone (10x7mm, no copper pour under ANT1)
2026-03-22 feat: widen 501 power traces to 0.4mm (was 0.2mm) + drawings restored
2026-03-22 fix: CRITICAL — NC net had 44 pins connected together, wasting autorouter resources. Now each NC pad has unique net.
2026-03-23 feat: overnight Freerouting — 4733 tracks (4290 traces + 443 vias), 9-hour run
2026-03-23 feat: Freerouting complete — auto-imported
2026-04-20 sidebar: parent projects toggle only, no chat load; sharper nesting
2026-05-03 slice-a: streaming input + four slash commands
    Make chat input feel terminal-class. Two behaviors:
    1. Allow Enter while streaming. Pressing Enter while a stream is in
    flight now stows the second message in a queued-followup slot
    (Zustand `queuedFollowup`) instead of firing a parallel POST.
    Visible "queued" badge shows the pending text. Auto-fires ~200ms
    after the in-flight stream finalizes. Re-checks state on fire so
2026-05-03 slice-c: inline diff for edit_file/write_file tool results
    Adds a minimal unified-diff renderer (DiffView.tsx, ~110 lines, Tailwind
    only, uses diffLines from the diff npm package) and wires it into
    ToolCallBlock for edit_file / write_file results. For edit_file, the
    old_string / new_string args are diffed directly. For write_file, the
    content renders as a "(new file)" all-additions block. Long diffs collapse
    to the first 50 lines with a "show N more lines" toggle.
2026-05-03 slice-b: @filename mention with project tree autocomplete + context injection
    Adds @-mention completion to the chat input and an /api/files/tree endpoint
    that surfaces an active project's file tree from the user's daemon device.
    Selected mentions are inserted into the message and also POSTed as
    'mentionedFiles' so the relay can read each file (8 KiB cap, [truncated]
    marker) and prepend a <mentioned-files>...</mentioned-files> bundle to
    the system prompt — agent sees the content up front, no round-trip
2026-05-03 slice-d: ws watchdog + reconnect badge + dogfood smoke test
    - thread-ws.ts: 15s heartbeat ping, exponential-backoff reconnect
    (1s -> 2s -> 4s -> 8s, cap 30s), connectionState observable
    ('connecting' | 'online' | 'reconnecting' | 'offline'). Promotes
    to 'offline' after 3 missed heartbeats.
    - chat/page.tsx: small badge top-right of the chat header. Online =
    green dot 'online', reconnecting = yellow dot, offline = red dot
2026-05-03 slice-d: smoke test trap-based cleanup + directional followup prompt
    - Move sentinel revert + thread-row deletion into an EXIT trap so the
    test cleans up even on early-exit failure (was leaving smoke-target.txt
    dirty and accumulating dead chat_threads rows).
    - Extend the followup message past a literal 'thanks' to a short courtesy
    + confirm-question. claude-opus reliably answers a bare 'thanks' with
    'You're welcome.' which is contextually correct but doesn't mention
2026-05-18 morning report 2026-05-18 + privacy.md fully synced
